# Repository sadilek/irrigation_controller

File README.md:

<h1 align="center">Irrigation controller</h1>

<p align="center">
  <b>Open hardware for a garden irrigation system run from Home Assistant:</b><br>
  sealed valve nodes in the ground, one buried cable, a controller in the shed.
</p>

<p align="center"><sub>The valve node, lid off. A render of the design files. No board has been made yet.</sub></p>

## What it is

Sprinkler valves sit in plastic boxes in the ground. A buried network cable (CAT-6) runs from the
shed through every box, one after the other. This project replaces the electronics on both ends of
that cable:

- **Valve node**, one per box: a small board in a sealed, 3D-printed enclosure that switches the
  24 V AC solenoid valves.
- **Controller**, in the shed: powers the cable and connects it to Home Assistant through ESPHome.

```mermaid
flowchart LR
    HA["Home Assistant"] -- Wi-Fi --- C["Controller<br/><i>in the shed</i>"]
    C -- "buried CAT-6<br/>RS485 · 12 V DC · 24 V AC" --- B1
    B1 --- B2 --- B3["…<br/><i>up to six boxes</i>"]
    subgraph B1 ["valve box"]
        direction TB
        N1["Valve node"] --- V1(("valve")) & V2(("valve"))
    end
    subgraph B2 ["valve box"]
        direction TB
        N2["Valve node"] --- V3(("valve"))
    end
```

The four pairs of the cable carry the data bus (RS485, Modbus RTU), 12 V DC for the logic,
24 V AC for the valves and one spare pair. Up to six boxes share less than 100 m of cable.

**Why new hardware.** The nodes in use today are mostly hobby modules on perfboard. A node keeps
a valve open for as long as it has power, even when the controller is gone. It cannot tell whether
a valve opened, and its address is compiled into its firmware. The new node fixes each of these and
is built to survive surges on the buried cable and damp in the valve box.

## The valve node

A two-layer board of 96 × 44 mm. The bus enters on one jack and leaves on the other; the valve
wires go into the spring terminal block on the right.

- **Switches the valves with triacs.** Two outputs are populated, there is room for four. One
  valve runs at a time, because the transformer and the cable are sized for one.
- **Keeps 24 V AC away from the logic.** Optocouplers are the only parts that cross from one side
  to the other. 24 V AC copper keeps at least 3 mm from everything else, and the design rule check
  enforces it on every build.
- **Knows whether a valve works.** Each output has a monitor that sees a broken valve wire before
  the valve is opened, and sees whether the output really conducts once it is.
- **Closes on its own.** All valves close after 60 seconds without a request from the controller, and
  any valve after two hours open. A watchdog resets a hung microcontroller, and a reset closes the
  valves.
- **Survives the cable.** TVS diodes clamp surges on each pair where it enters the board and do
  not wear out with each surge. A short in one node's supply or valve wiring blows a fuse in that
  node instead of taking down the others.
- **One firmware for all nodes.** The address is set with a DIP switch on the board.
- **Nothing to solder.** JLCPCB assembles every part, including the connectors. About $22 per board
  in a batch of five, before shipping and import tax.

<p align="center"><sub>Copper by net class. Orange carries 24 V AC, blue and green are logic; the hatched strip in between holds no copper on either layer.</sub></p>

## The enclosure

Everything mechanical is printed: base, lid and nuts in ASA, gasket and cable seals in TPU. Only
the screws and the brass inserts they go into are bought.

- **All three cables enter through one wall,** which keeps the box at 114 × 93 × 34 mm.
- **A crimped network plug fits through the entry.** The soft seal of a bus entry is slit, so it
  goes onto the cable after the plug has passed. Tightening the nut pushes the seal into a cone,
  which squeezes it onto the cable.
- **The lid stops on the rim.** A ridge under the lid presses into a printed gasket by a set
  amount, however hard the screws are turned.
- **Every plug can be pulled with the board installed.** An automated collision check proves that
  board, plugs and enclosure do not overlap.

<p align="center"><sub>Section through a bus entry: the stiff cable runs in a straight line through the seal into its jack.</sub></p>

## Everything is source text

No one draws this design in KiCad or a CAD program. Each board is a set of text files, and one
command turns them into everything a manufacturer needs:

| Step | Tool | Source |
|---|---|---|
| Schematic | [Zener](https://github.com/diodeinc/pcb), generated into KiCad 10 | `boards/<board>/<board>.zen` |
| Placement and routing | Python against KiCad's `pcbnew`, with a small grid router | `boards/<board>/layout.py` |
| Checks | KiCad's electrical and design rule checks, with the board's own rules | generated |
| Fabrication data | Gerbers, bill of materials and placement file for JLCPCB, board STEP | generated |
| Enclosure | [build123d](https://github.com/gumyr/build123d) | `boards/<board>/enclosure.py` |
| Fit | Collision check of the populated board against every enclosure part | generated |

Board and enclosure share one file of outline, mounting holes and connector positions
(`mech.json`), so they cannot drift apart. `make selftest` breaks the design on purpose (a lid
pushed into a jack, a ground track next to 24 V AC copper) and expects the checks to fail, so a
clean report means something. An AI coding agent does the design work in these files. The owner
reviews each board at three hold points (specification, schematic, layout and enclosure) and
places every order.

## Status

- **Valve node:** specification, schematic, layout, fabrication data and enclosure are done and
  were signed off by 2026-11-15. A change made the same day (bus termination moved to the
  controller, nothing left to solder by hand) awaits sign-off of schematic and
  layout. The enclosure had a first test print; nothing is ordered yet, and no real board exists. The firmware is not written
  yet.
- **Controller:** not designed yet. Until it is, the new nodes run with the existing controller.

## Quick start

Requires macOS on Apple Silicon, KiCad 10 in `/Applications`, [`uv`](https://docs.astral.sh/uv/) and `make`.

```bash
make setup                  # pinned tools into .tools/, nothing installed system-wide
make all                    # throwaway board: schematic -> checks -> layout -> fabrication data -> enclosure -> collision check
make all BOARD=valve-node   # the same for the valve node, about two minutes
make help                   # one command per output
```

Outputs land in `build/<board>/`. The generated KiCad project in `boards/<board>/eda/` opens in
KiCad 10 without any of the tools above.

## Documentation

| Question | Page |
|---|---|
| How does the chain work, what does each command produce, where is it weak? | [`docs/toolchain.md`](docs/toolchain.md) |
| What runs on the cable: wiring, addresses, registers, timing? | [`docs/bus-protocol.md`](docs/bus-protocol.md) |
| What is installed today, and what is wrong with it? | [`docs/existing-system.md`](docs/existing-system.md) |
| What does the valve node have to do, and why these parts? | [`docs/valve-node-spec.md`](docs/valve-node-spec.md) |
| What did the schematic add, and what was checked? | [`docs/valve-node-schematic.md`](docs/valve-node-schematic.md) |
| How does the enclosure seal, and how is it printed? | [`docs/valve-node-enclosure.md`](docs/valve-node-enclosure.md) |
| Where do the parts sit, how is 24 V AC kept from the logic, what does an order cost? | [`docs/valve-node-layout.md`](docs/valve-node-layout.md) |
| What does the valve node do on the bus, and how is its firmware built and tested? | [`docs/valve-node-firmware.md`](docs/valve-node-firmware.md) |
| How do I add a part and map it to a JLCPCB part number? | [`lib/README.md`](lib/README.md) |
| Which license covers what? | [`docs/license.md`](docs/license.md) |
| Rules and conventions for agents and contributors | [`CLAUDE.md`](CLAUDE.md) |

## License

Hardware: [CERN-OHL-P-2.0](LICENSES/CERN-OHL-P-2.0.txt). Software: [MIT](LICENSES/MIT.txt).
Documentation: [CC-BY-4.0](LICENSES/CC-BY-4.0.txt). Details and exceptions in [`docs/license.md`](docs/license.md).

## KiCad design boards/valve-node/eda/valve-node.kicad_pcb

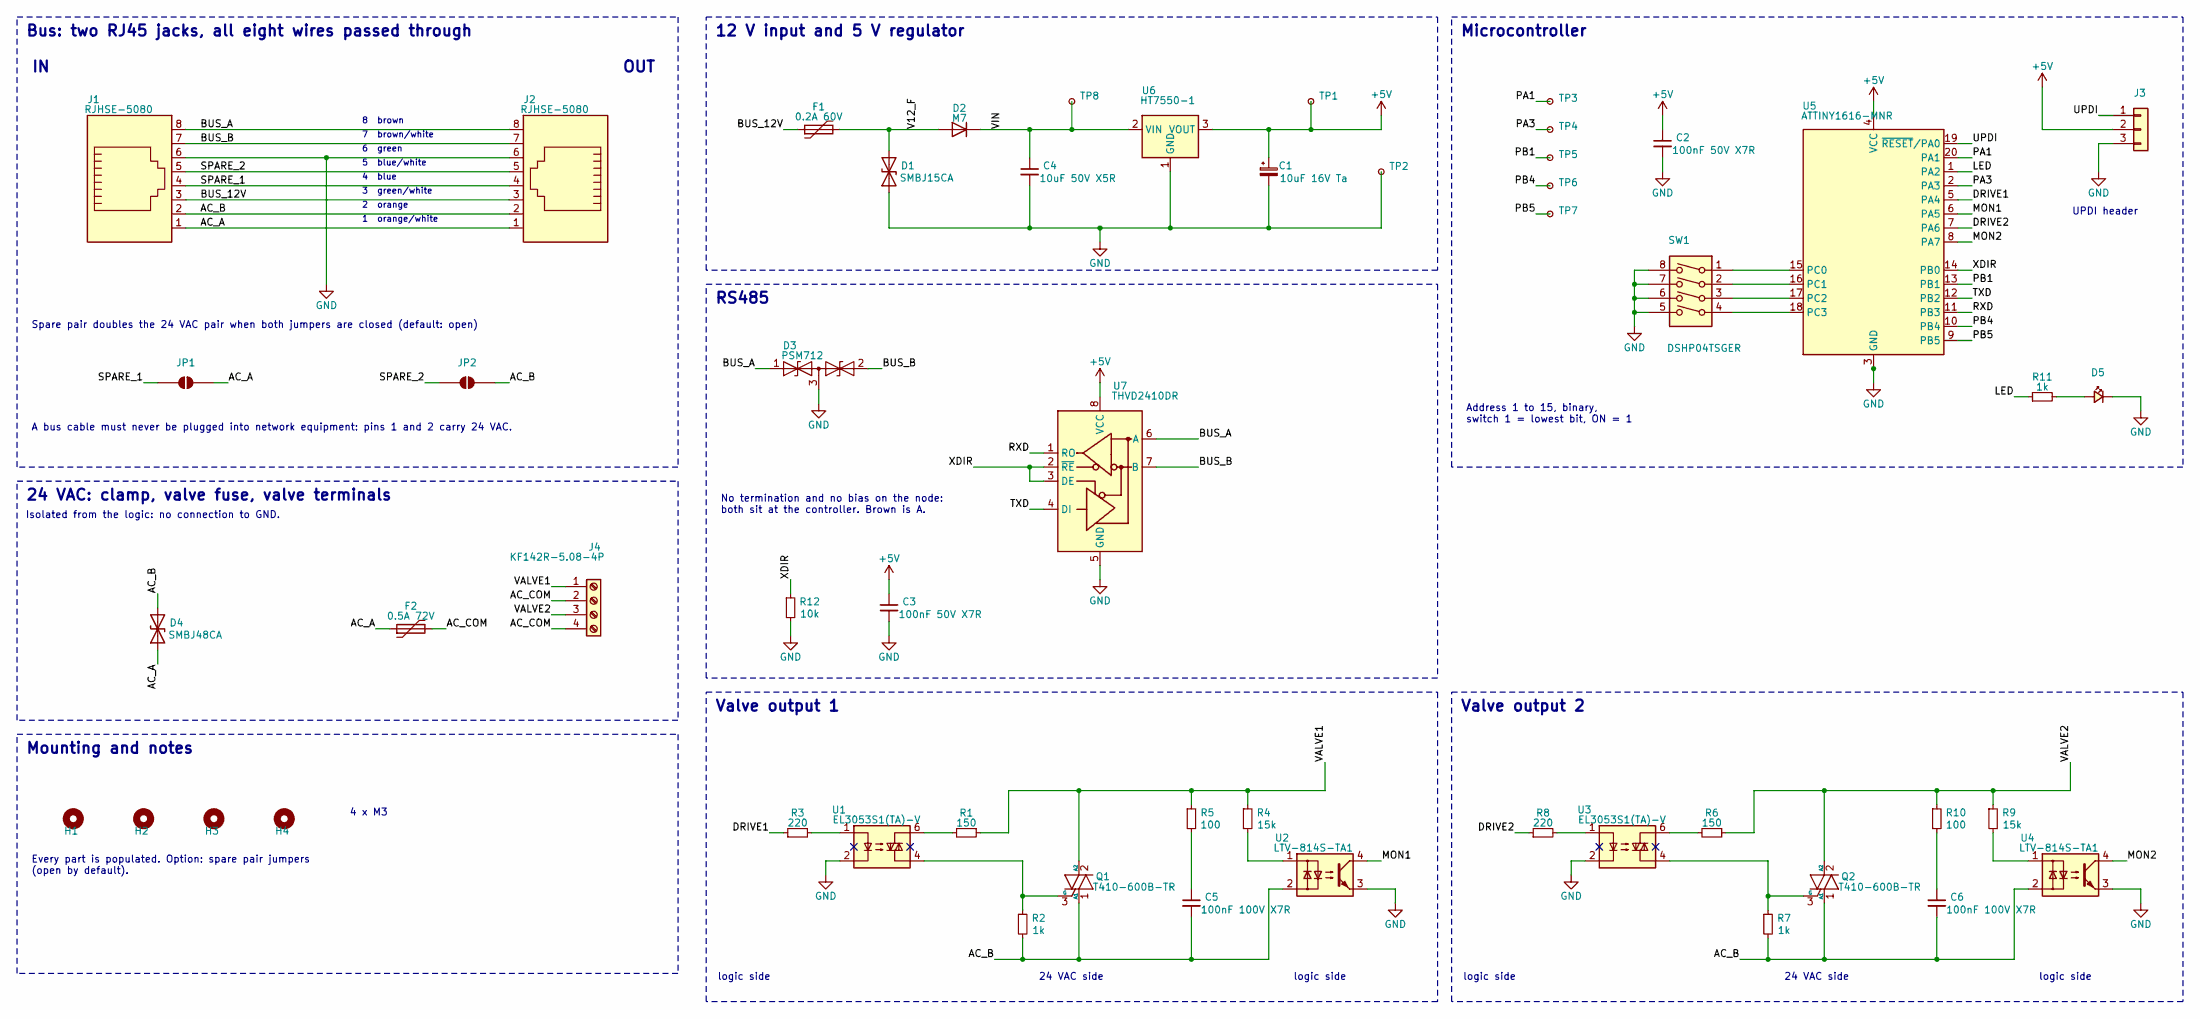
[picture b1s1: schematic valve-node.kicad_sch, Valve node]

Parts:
C1: 10uF 16V Ta; CP_EIA-3216-18_Kemet-A
C2, C3: 100nF 50V X7R; C_0603_1608Metric
C4: 10uF 50V X5R; C_1206_3216Metric
C5, C6: 100nF 100V X7R; C_0805_2012Metric
D1: SMBJ15CA; D_SMB
D2: M7; D_SMA
D3: PSM712; SOT-23
D4: SMBJ48CA; D_SMB
D5: LED GREEN; LED_0603_1608Metric
F1: 0.2A 60V; Fuse_1812_4532Metric
F2: 0.5A 72V; Fuse_1812_4532Metric
H1, H2, H3, H4: M3 DIN965 Mechanical; MountingHole_3.2mm_M3_DIN965
J1, J2: RJHSE-5080; RJ45-TH_RJHSE-5080
J3: 2.54mm 3 x 1 THT Vertical Male; PinHeader_1x03_P2.54mm_Vertical
J4: KF142R-5.08-4P; CONN-TH_4P-P5.08_KF142R-5.08-4P
JP1, JP2: SolderJumper_2_Open; SolderJumper-2_P1.3mm_Open_Pad1.0x1.5mm
Q1, Q2: T410-600B-TR; TO-252-2
R1, R6: 150; R_0805_2012Metric
R2, R7, R11: 1k; R_0603_1608Metric
R3, R8: 220; R_0603_1608Metric
R4, R9: 15k; R_0805_2012Metric
R5, R10: 100; R_0805_2012Metric
R12: 10k; R_0603_1608Metric
SW1: DSHP04TSGER; SW_DIP_SPSTx04_Slide_KingTek_DSHP04TS_W7.62mm_P1.27mm
TP1, TP2, TP3, TP4, TP5, TP6, TP7, TP8: TestPoint_Small; TestPoint_Pad_D1.5mm
U1, U3: EL3053S1(TA)-V; SMDIP-6_W9.53mm
U2, U4: LTV-814S-TA1; SMDIP-4_W9.53mm
U5: ATTINY1616-MNR; VQFN-20-1EP_3x3mm_P0.4mm_EP1.7x1.7mm
U6: HT7550-1; SOT-89-3
U7: THVD2410DR; SOIC-8_3.9x4.9mm_P1.27mm

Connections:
+5V: C1.1, C2.1, C3.1, J3.2, TP1.1, U5.4 (VCC), U6.3 (VOUT), U7.8 (VCC)
AC_A: D4.1 (A1), F2.1, J1.1, J2.1, JP1.2 (B)
AC_B: C5.2, C6.2, D4.2 (A2), J1.2, J2.2, JP2.2 (B), Q1.1 (A1), Q2.1 (A1), R2.2, R7.2, U2.2, U4.2
AC_COM: F2.2, J4.2, J4.4
ADDR1: SW1.1, U5.15 (PC0)
ADDR2: SW1.2, U5.16 (PC1)
ADDR3: SW1.3, U5.17 (PC2)
ADDR4: SW1.4, U5.18 (PC3)
BUS_12V: F1.1, J1.3, J2.3
BUS_A: D3.1 (A1), J1.8, J2.8, U7.6 (A)
BUS_B: D3.2 (A2), J1.7, J2.7, U7.7 (B)
DRIVE1: R3.1, U5.5 (PA4)
DRIVE2: R8.1, U5.7 (PA6)
GND: C1.2, C2.2, C3.2, C4.2, D1.1 (A1), D3.3 (common), D5.1 (K), J1.6, J2.6, J3.3, R12.2, SW1.5, SW1.6, SW1.7, SW1.8, TP2.1, U1.2, U2.3, U3.2, U4.3, U5.3 (GND), U5.21 (GND), U6.1 (GND), U7.5 (GND)
LED: R11.1, U5.1 (PA2)
LED_A: D5.2 (A), R11.2
MON1: U2.4, U5.6 (PA5)
MON2: U4.4, U5.8 (PA7)
OUT1.GATE: Q1.3 (G), R2.1, U1.4
OUT1.LED_A: R3.2, U1.1
OUT1.MON_LED: R4.2, U2.1
OUT1.NC_U_DRV_NC3: U1.3 (NC3)
OUT1.NC_U_DRV_NC5: U1.5 (NC5)
OUT1.OPTO: R1.2, U1.6
OUT1.SNUB: C5.1, R5.2
OUT2.GATE: Q2.3 (G), R7.1, U3.4
OUT2.LED_A: R8.2, U3.1
OUT2.MON_LED: R9.2, U4.1
OUT2.NC_U_DRV_NC3: U3.3 (NC3)
OUT2.NC_U_DRV_NC5: U3.5 (NC5)
OUT2.OPTO: R6.2, U3.6
OUT2.SNUB: C6.1, R10.2
PA1: TP3.1, U5.20 (PA1)
PA3: TP4.1, U5.2 (PA3)
PB1: TP5.1, U5.13 (PB1)
PB4: TP6.1, U5.10 (PB4)
PB5: TP7.1, U5.9 (PB5)
RXD: U5.11 (PB3), U7.1 (RO)
SPARE_1: J1.4, J2.4, JP1.1 (A)
SPARE_2: J1.5, J2.5, JP2.1 (A)
TXD: U5.12 (PB2), U7.4 (DI)
UPDI: J3.1, U5.19 (~RESET/PA0)
V12_F: D1.2 (A2), D2.2 (A), F1.2
VALVE1: J4.1, Q1.2 (A2), R1.1, R4.1, R5.1
VALVE2: J4.3, Q2.2 (A2), R6.1, R9.1, R10.1
VIN: C4.1, D2.1 (K), TP8.1, U6.2 (VIN)
XDIR: R12.1, U5.14 (PB0), U7.2 (~RE), U7.3 (DE)

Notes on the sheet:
Bus: two RJ45 jacks, all eight wires passed through
1 orange/white
2 orange
3 green/white
4 blue
5 blue/white
6 green
7 brown/white
8 brown
OUT
Spare pair doubles the 24 VAC pair when both jumpers are closed (default: open)
A bus cable must never be plugged into network equipment: pins 1 and 2 carry 24 VAC.
12 V input and 5 V regulator
RS485
No termination and no bias on the node: both sit at the controller. Brown is A.
Microcontroller
Address 1 to 15, binary, switch 1 = lowest bit, ON = 1
UPDI header
24 VAC: clamp, valve fuse, valve terminals
Isolated from the logic: no connection to GND.
Mounting and notes
4 x M3
Every part is populated. Option: spare pair jumpers (open by default).
Valve output 1
logic side
24 VAC side
Valve output 2

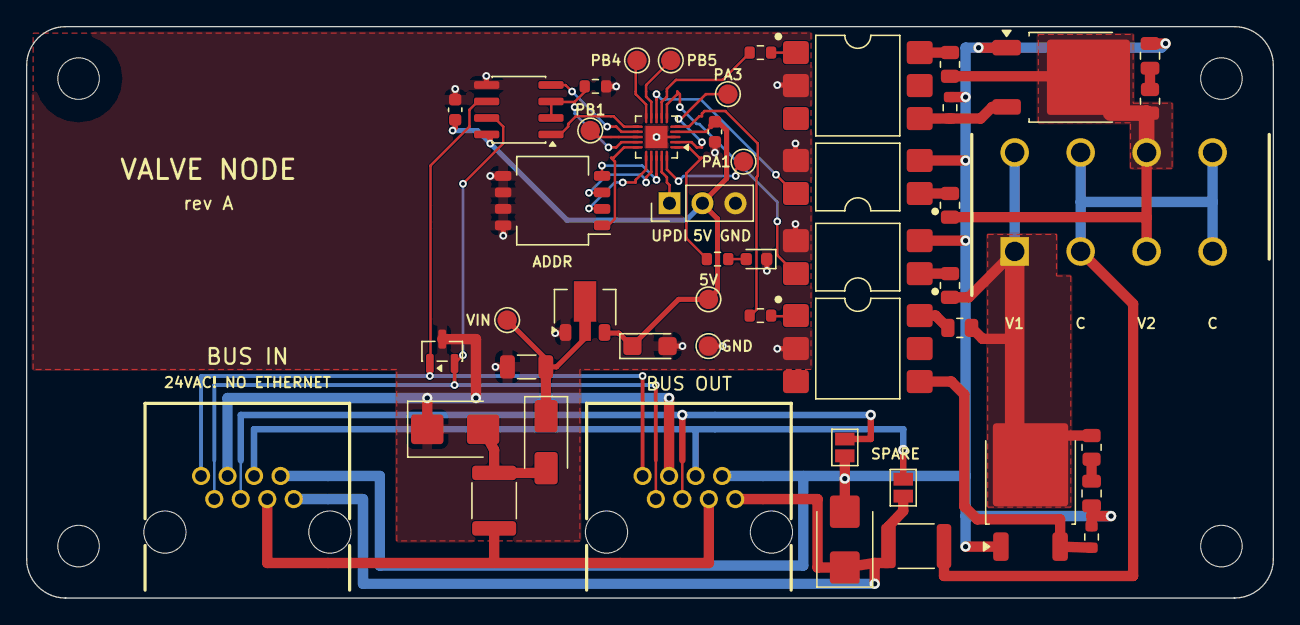
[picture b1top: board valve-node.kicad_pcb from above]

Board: 2 copper layers, 96.0 x 44.0 mm, 53 parts (0 on the bottom side), 43 nets.

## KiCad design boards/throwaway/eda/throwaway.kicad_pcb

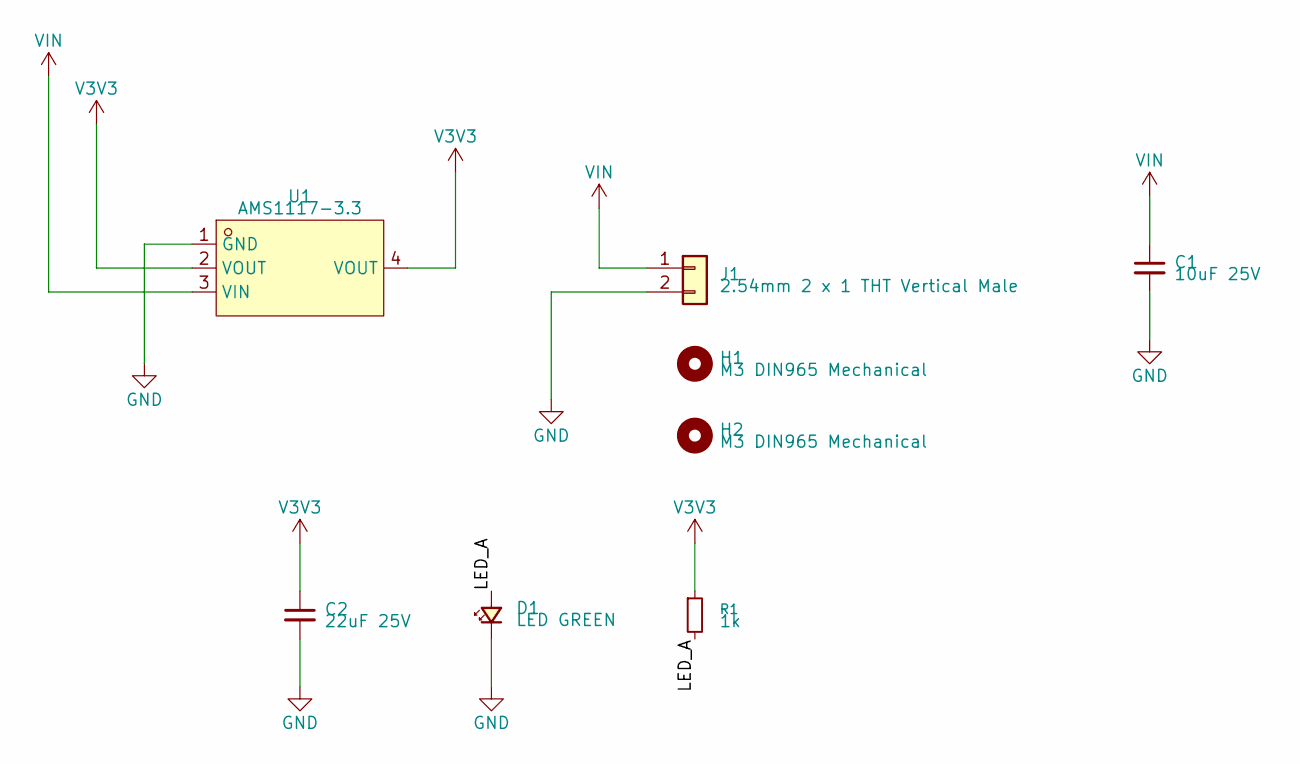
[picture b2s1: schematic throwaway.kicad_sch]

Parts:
C1: 10uF 25V; C_0805_2012Metric
C2: 22uF 25V; C_0805_2012Metric
D1: LED GREEN; LED_0603_1608Metric
H1, H2: M3 DIN965 Mechanical; MountingHole_3.2mm_M3_DIN965
J1: 2.54mm 2 x 1 THT Vertical Male; PinHeader_1x02_P2.54mm_Vertical
R1: 1k; R_0603_1608Metric
U1: AMS1117-3.3; SOT-223-3_L6.5-W3.4-P2.30-LS7.0-BR

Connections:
GND: C1.2, C2.2, D1.1 (K), J1.2, U1.1 (GND)
LED_A: D1.2 (A), R1.2
V3V3: C2.1, R1.1, U1.2 (VOUT), U1.4 (VOUT)
VIN: C1.1, J1.1, U1.3 (VIN)

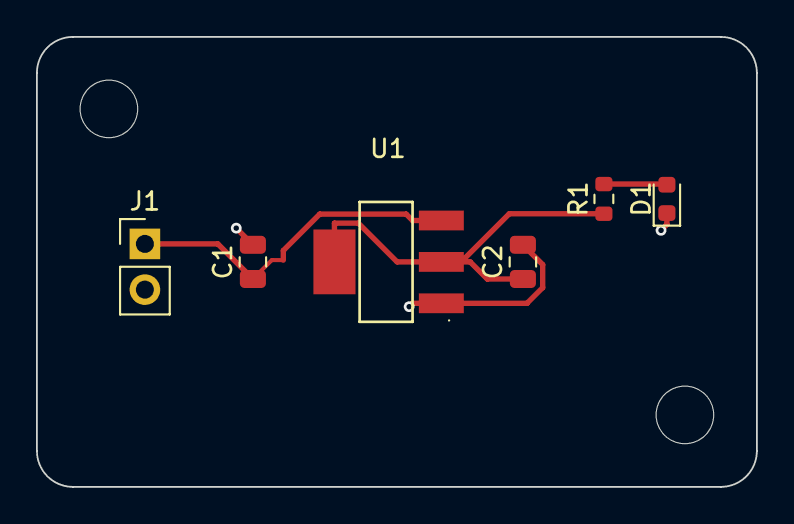
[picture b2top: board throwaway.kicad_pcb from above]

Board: 2 copper layers, 40.0 x 25.0 mm, 8 parts (0 on the bottom side), 4 nets.

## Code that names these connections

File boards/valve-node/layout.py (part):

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    L.text(label, valve_pin_x[n], 22.85, 0.8)
L.text("SPARE", 66.9, 32.9, 0.8)
L.text("ADDR", 40.5, 18.1, 0.8)
for label, x in (("UPDI", 49.5), ("5V", 52.04), ("GND", 54.58)):
    L.text(label, x, 16.1, 0.8)
for label, name, dx, dy in (("5V", "TP_5V", 0, -1.5), ("GND", "TP_GND", 2.2, 0), ("VIN", "TP_VIN", -2.2, 0), ("PB4", "TP_PB4", -2.4, 0),
                            ("PB5", "TP_PB5", 2.4, 0), ("PB1", "TP_PB1", 0, -1.6), ("PA3", "TP_PA3", 0, -1.5), ("PA1", "TP_PA1", -2.1, 0)):
    x, y = L.pad(name, 1)
    L.text(label, x + dx, y + dy, 0.8)
# Pin 1 of each optocoupler: a dot at the pin's outer corner. Their own mark, a notch in the
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# At the OUT jack each lane ends in a via and drops to its pin on the top layer. The two pins of
# the inner row (B, spare 2) pass between two pads of the outer row with a 0.2 mm track.
LANE = {"BUS_A": 26.9, "BUS_B": 27.6, "GND": 28.6, "SPARE_2": 29.9, "SPARE_1": 31.0}
for net, pin, width, inner_row in (("BUS_A", 8, 0.3, False), ("BUS_B", 7, 0.3, True), ("GND", 6, 0.8, False), ("SPARE_2", 5, 0.5, True)):
    y = LANE[net]
    for jack, layer in ((p, B), (q, F)):
        x, ypin = jack[pin]
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for n, net, layer in ((1, "VALVE1", B), (2, "AC_COM", B), (3, "VALVE2", F), (4, "AC_COM", B)):
    L.track(net, layer, [valve_pin[n], front_pin[n]], 0.8)
y_mid = valve_pin[2][1] + PIN_ROWS / 2
L.track("AC_COM", B, [(valve_pin[2][0], y_mid), (valve_pin[4][0], y_mid)], 0.8)
# Fused valve common: along the board edge, then up past output 1 to the front pin of pole 2.
X_COM, Y_COM = 85.2, 42.3
L.track("AC_COM", F, [f2_com, (f2_com[0], Y_COM), (X_COM, Y_COM), (X_COM, front_pin[2][1] + X_COM - front_pin[2][0]), front_pin[2]], 0.8)
# Spare pair: its lanes continue to the two open jumpers.
jp1_sp, jp1_ac = L.pad("JP_SPARE_1", 1), L.pad("JP_SPARE_1", 2)
L.track("SPARE_2", B, [(q[5][0], LANE["SPARE_2"]), (PASS_EDGE, LANE["SPARE_2"])], 0.5)
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# monitor resistor under the block, between its pin rows, to pole 3.
r_gate, r_snub, r_mon = P("R_GATE", 1), P("R_SNUB", 1), P("R_MON", 1)
L.track("VALVE2", F, [r_gate, (tab[0] - 2.2, r_gate[1])], 0.8)
L.track("VALVE2", F, [(tab[0] + 1.7, r_snub[1]), (valve_pin[3][0], r_snub[1]), valve_pin[3]], 1.2)
L.track("VALVE2", F, [r_mon, (valve_pin[3][0], r_mon[1])], 0.8)
# A copper area that also cools the triac (ST DocID7699 Rev 9: 70 K/W assumes 0.5 cm2 of copper under the tab).
L.zone("VALVE2", F, outline=[(77.9, 0.6), (85.2, 0.6), (85.2, 5.9), (88.2, 5.9), (88.2, 10.9), (85.0, 10.9), (85.0, 7.4), (77.9, 7.4)], solid=True)

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L.track("OUT1.SNUB", F, [P("R_SNUB", 2), P("C_SNUB", 1)], 0.8)
# The valve node: pole 1 straight into the tab; gate and monitor resistors; tab to the snubber resistor.
r_gate, r_snub, r_mon = P("R_GATE", 1), P("R_SNUB", 1), P("R_MON", 1)
L.track("VALVE1", F, [front_pin[1], (front_pin[1][0], tab[1] - 2.2)], 1.5)
L.track("VALVE1", F, [r_gate, (r_gate[0] + 0.84, r_gate[1] + 0.84), (front_pin[1][0], r_gate[1] + 0.84)], 0.8)
L.track("VALVE1", F, [r_mon, (front_pin[1][0] - (r_mon[1] - front_pin[1][1]), r_mon[1]), front_pin[1]], 0.8)
L.track("VALVE1", F, [(tab[0] + 2.2, r_snub[1]), r_snub], 0.8)
L.zone("VALVE1", F, outline=[(74.0, 16.0), (79.3, 16.0), (79.3, 19.2), (80.4, 19.2), (80.4, 37.0), (74.0, 37.0)], solid=True)

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R.route("+5V", width=0.4, only=["C_MCU.1", "J_UPDI.2"])  # likewise: output 2's signals pass around this capacitor
for net in ("TXD", "RXD", "XDIR", "ADDR1", "ADDR2", "ADDR3", "ADDR4", "UPDI",
            "DRIVE2", "MON2", "OUT2.LED_A", "DRIVE1", "MON1", "OUT1.LED_A", "LED", "LED_A",
            "BUS_A", "BUS_B", "PB1", "PB4", "PB5", "PA3", "PA1"):
    R.route(net)
for net in ("VIN", "+5V"):
    R.route(net, width=0.4)
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
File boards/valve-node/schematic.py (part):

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    S.wire("C_5V.2", (x + 101.6, rail))
    S.wire((x + 71.12, rail), (x + 71.12, rail + G))
    S.power_symbol((x + 71.12, rail + G), net="GND")
    S.label((x + 38.1, yl), (0, -1), net="V12_F")
    S.label((x + 53.34, yl), (0, -1), net="VIN")


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    # Driver enable and receiver enable on one net: the node does not hear its own answer.
    S.wire("U_RS485.2", (lx - 5 * G, uy - G))
    S.wire("U_RS485.3", (lx - G, uy), (lx - G, uy - G))
    S.label((lx - 5 * G, uy - G), (-1, 0), net="XDIR")
    S.place("R_XDIR", x + 15.24, y + 58.42)
    S.place("C_RS485", x + 33.02, y + 58.42, value=(1.9, 1.2))

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    # the controller.
    S.wire("U_RS485.6", (rx + 3 * G, ya))
    S.wire("U_RS485.7", (rx + 3 * G, yb))
    S.label((rx + 3 * G, ya), (1, 0), net="BUS_A")
    S.label((rx + 3 * G, yb), (1, 0), net="BUS_B")
    S.place("D3", x + 20.32, y + 15.24)
    S.text(x + G, y + 38.1, "No termination and no bias on the node:\nboth sit at the controller. Brown is A.", size=1.27)

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    S.wire((x + 54.61, top), (x + 111.76, top), (x + 111.76, top - 2 * G))
    S.label((x + 111.76, top - 2 * G), (0, -1), net="VALVE%d" % n)  # to the valve terminal block
    S.wire((x + 52.07, bottom), (x + 101.6, bottom))
    S.label((x + 52.07, bottom), (-1, 0), net="AC_B")
    S.text(x + 2.0, y + 50.8, "logic side", size=1.27)
    S.text(x + 106.0, y + 50.8, "logic side", size=1.27)
    S.text(x + 60.0, y + 50.8, "24 VAC side", size=1.27)
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
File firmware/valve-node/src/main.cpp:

// Valve node on the ATtiny1616: clock, pins, serial port, timer and watchdog around the core
// in core/valve_node.cpp. Written directly on avr-libc; no framework.
// Pin assignment: docs/valve-node-spec.md, "Microcontroller and pin assignment".
// Register and bit names: Microchip ATtiny1614/1616/1617 datasheet, DS40002204A.

#include <avr/interrupt.h>
#include <avr/io.h>
#include <avr/wdt.h>
#include <util/atomic.h>
#include <util/delay.h>

#include "valve_node.h"

// Port A
static const uint8_t LED = PIN2_bm;
static const uint8_t DRIVE1 = PIN4_bm;
static const uint8_t MONITOR1 = PIN5_bm;
static const uint8_t DRIVE2 = PIN6_bm;
static const uint8_t MONITOR2 = PIN7_bm;
// Port B
static const uint8_t XDIR = PIN0_bm;
static const uint8_t TXD = PIN2_bm;
static const uint8_t RXD = PIN3_bm;
// Port C: address switch on pins 0 to 3, switch 1 on pin 0
static const uint8_t ADDRESS = PIN0_bm | PIN1_bm | PIN2_bm | PIN3_bm;

static valve_node::ValveNode node;

// --- Time: timer B0 overflows once a millisecond -------------------------------------------------

static const uint16_t TICKS_PER_MS = F_CPU / 1000;
static volatile uint32_t milliseconds;

ISR(TCB0_INT_vect) {
  milliseconds++;
  TCB0.INTFLAGS = TCB_CAPT_bm;
}

static uint32_t millis() {
  uint32_t ms;
  ATOMIC_BLOCK(ATOMIC_RESTORESTATE) { ms = milliseconds; }
  return ms;
}

static uint32_t micros() {
  uint32_t ms;
  uint16_t ticks;
  ATOMIC_BLOCK(ATOMIC_RESTORESTATE) {
    ms = milliseconds;
    ticks = TCB0.CNT;
    // The timer wrapped while interrupts were off: count that millisecond and read again.
    if (TCB0.INTFLAGS & TCB_CAPT_bm) {
      ms++;
      ticks = TCB0.CNT;
    }
  }
  return ms * 1000UL + ticks / (TICKS_PER_MS / 1000);
}

// --- Serial port: USART0 in RS-485 mode, both directions through interrupts ----------------------

static volatile uint8_t rx_buffer[64];  // size is a power of two
static volatile uint8_t rx_head, rx_tail;
static uint8_t tx_buffer[64];
static volatile uint8_t tx_length, tx_position;

ISR(USART0_RXC_vect) {
  uint8_t flags = USART0.RXDATAH;
  uint8_t byte = USART0.RXDATAL;
  // A byte with a framing error is kept: it damages the checksum, and the frame is then counted.
  (void)flags;
  uint8_t next = (uint8_t)(rx_head + 1) % sizeof(rx_buffer);
  if (next != rx_tail) {
    rx_buffer[rx_head] = byte;
    rx_head = next;
  }
}

ISR(USART0_DRE_vect) {
  USART0.TXDATAL = tx_buffer[tx_position++];
  if (tx_position == tx_length) USART0.CTRLA &= (uint8_t)~USART_DREIE_bm;
}

static void send(const uint8_t* data, uint8_t length) {
  for (uint8_t i = 0; i < length; i++) tx_buffer[i] = data[i];
  tx_position = 0;
  tx_length = length;
  USART0.CTRLA |= USART_DREIE_bm;
}

static void serial_begin() {
  // The factory measured this chip's oscillator error at 5 V, in steps of 1/1024; correct the
  // baud rate by it (datasheet 24.3.2.1 and the SIGROW description).
  int8_t error = (int8_t)SIGROW.OSC20ERR5V;
  uint32_t baud = (4UL * F_CPU + 9600 / 2) / 9600;  // 64 * F_CPU / (16 * baud rate)
  USART0.BAUD = (uint16_t)(baud * (uint32_t)(1024 + error) / 1024);
  USART0.CTRLC = USART_CHSIZE_8BIT_gc;  // asynchronous, no parity, one stop bit
  // The pull-up keeps RXD idle while the node sends: the transceiver's receiver is off then.
  PORTB.PIN3CTRL = PORT_PULLUPEN_bm;
  VPORTB.OUT |= TXD;
  VPORTB.OUT &= (uint8_t)~XDIR;
  VPORTB.DIR |= TXD | XDIR;
  VPORTB.DIR &= (uint8_t)~RXD;
  // RS-485 mode: the USART drives XDIR high from one bit before a frame until its last stop bit.
  USART0.CTRLA = USART_RXCIE_bm | USART_RS485_EXT_gc;
  USART0.CTRLB = USART_RXEN_bm | USART_TXEN_bm;
}

// --- Start-up ------------------------------------------------------------------------------------

// The WDTCFG fuse starts the watchdog at reset and locks it. If a chip was flashed without its
// fuses, start it here; either way lock it, so that nothing the firmware does later can stop it.
static void lock_watchdog() {
  if ((WDT.CTRLA & WDT_PERIOD_gm) == 0) _PROTECTED_WRITE(WDT.CTRLA, WDT_PERIOD_2KCLK_gc);
  while (WDT.STATUS & WDT_SYNCBUSY_bm) {}
  _PROTECTED_WRITE(WDT.STATUS, WDT_LOCK_bm);
}

int main() {
  lock_watchdog();
  uint8_t reset_cause = RSTCTRL.RSTFR;
  RSTCTRL.RSTFR = reset_cause;  // writing the flags back clears them

  // 5 MHz: the 20 MHz oscillator divided by four.
  _PROTECTED_WRITE(CLKCTRL.MCLKCTRLB, CLKCTRL_PDIV_4X_gc | CLKCTRL_PEN_bm);

  // Pins are inputs after reset, so the valves are closed. Low before they become outputs.
  VPORTA.OUT &= (uint8_t)~(DRIVE1 | DRIVE2 | LED);
  VPORTA.DIR |= DRIVE1 | DRIVE2 | LED;
  PORTA.PIN5CTRL = PORT_PULLUPEN_bm;  // monitors: the optocoupler pulls low
  PORTA.PIN7CTRL = PORT_PULLUPEN_bm;
  // Unused pins, on test pads: pull-up, so they do not float.
  PORTA.PIN1CTRL = PORT_PULLUPEN_bm;
  PORTA.PIN3CTRL = PORT_PULLUPEN_bm;
  PORTB.PIN1CTRL = PORT_PULLUPEN_bm;
  PORTB.PIN4CTRL = PORT_PULLUPEN_bm;
  PORTB.PIN5CTRL = PORT_PULLUPEN_bm;
  // Address switch: a closed switch pulls its pin to ground.
  PORTC.PIN0CTRL = PORT_PULLUPEN_bm;
  PORTC.PIN1CTRL = PORT_PULLUPEN_bm;
  PORTC.PIN2CTRL = PORT_PULLUPEN_bm;
  PORTC.PIN3CTRL = PORT_PULLUPEN_bm;

  // Switch 1 is the lowest bit. Read once, at reset.
  _delay_ms(2);
  uint8_t address = (uint8_t)(~VPORTC.IN) & ADDRESS;

  TCB0.CCMP = TICKS_PER_MS - 1;
  TCB0.INTCTRL = TCB_CAPT_bm;
  TCB0.CTRLA = TCB_CLKSEL_CLKDIV1_gc | TCB_ENABLE_bm;  // periodic interrupt mode is the default

  serial_begin();
  node.begin(address, reset_cause, 0);
  sei();

  for (;;) {
    wdt_reset();

    uint32_t now_ms = millis();
    while (rx_tail != rx_head) {
      uint8_t byte = rx_buffer[rx_tail];
      rx_tail = (uint8_t)(rx_tail + 1) % sizeof(rx_buffer);
      node.receive(byte, micros());
    }
    uint8_t length = node.poll(now_ms, micros());
    if (length) send(node.response(), length);

    uint8_t out = VPORTA.OUT & (uint8_t)~(DRIVE1 | DRIVE2 | LED);
    if (node.driven(0)) out |= DRIVE1;
    if (node.driven(1)) out |= DRIVE2;
    if (node.led(now_ms)) out |= LED;
    VPORTA.OUT = out;

    // The optocoupler pulls the pin low while voltage lies across the triac.
    uint8_t in = VPORTA.IN;
    node.monitor(0, !(in & MONITOR1));
    node.monitor(1, !(in & MONITOR2));
  }
}
